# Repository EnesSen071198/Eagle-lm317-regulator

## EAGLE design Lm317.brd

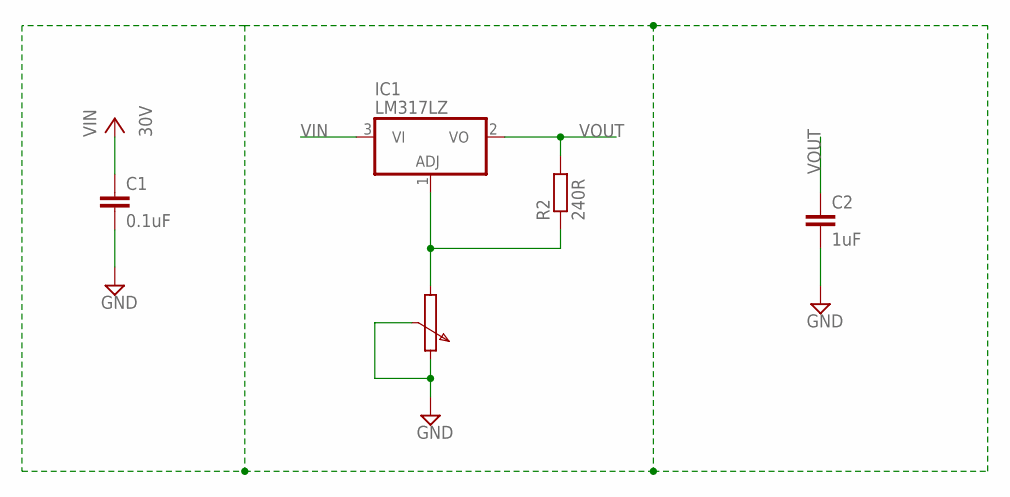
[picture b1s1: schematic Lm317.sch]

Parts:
C1: 0.1uF; C050-025X075
C2: 1uF; C050-025X075
IC1: LM317LZ; TO92
R2: 240R; 0207/10

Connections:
GND: C1.2, C2.2
unnamed: IC1.1 (ADJ), R2.1
VIN: C1.1, IC1.3 (VI)
VOUT: C2.1, IC1.2 (VO), R2.2

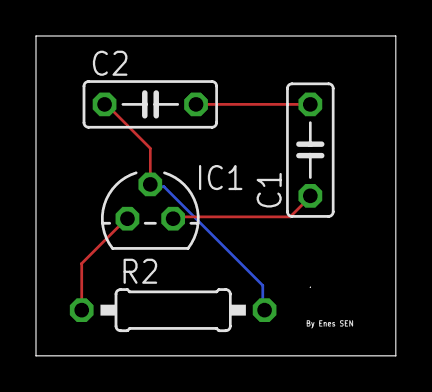
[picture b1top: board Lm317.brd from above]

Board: 2 copper layers, 20.0 x 17.8 mm, 5 parts (0 on the bottom side), 4 nets.

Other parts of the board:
U$1: LOGO

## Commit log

2025-05-19 Create Proteus-Simulasyon
